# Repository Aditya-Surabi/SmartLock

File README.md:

# SmartLock

Smartphone controlled door locking system.

Hardware List
- Arduino Nano
- ESP8266
- Servo
- LM317 LDO 3.3V Voltage Regulator
- Deadbolt
- Battery (Capacity TBD)

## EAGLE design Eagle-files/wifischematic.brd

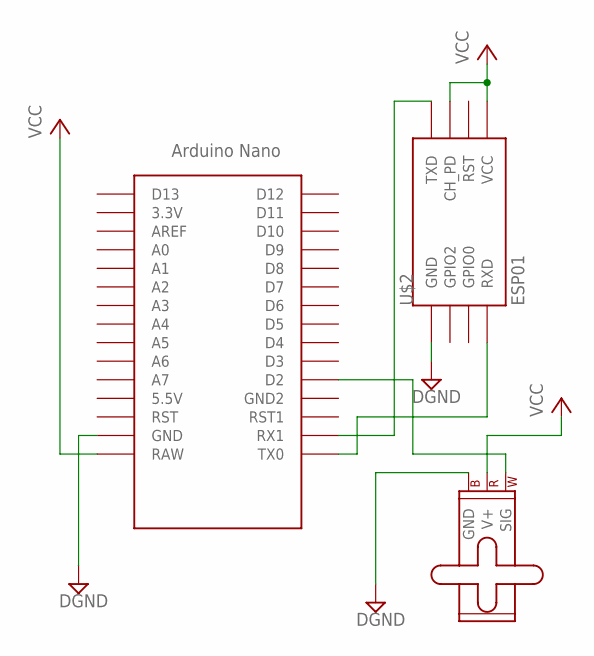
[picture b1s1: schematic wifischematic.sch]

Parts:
M1: SMALL_SERVO; 1X03
U$1: NANO
U$2: ESP01

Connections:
DGND: M1.3 (GND), U$1.GND, U$2.GND
unnamed: U$1.TX0, U$2.RX (RXD)
unnamed: U$1.RX1, U$2.TX (TXD)
unnamed: M1.1 (SIG), U$1.D2
VCC: M1.2 (V+), U$1.RAW, U$2.CH_PD, U$2.VCC

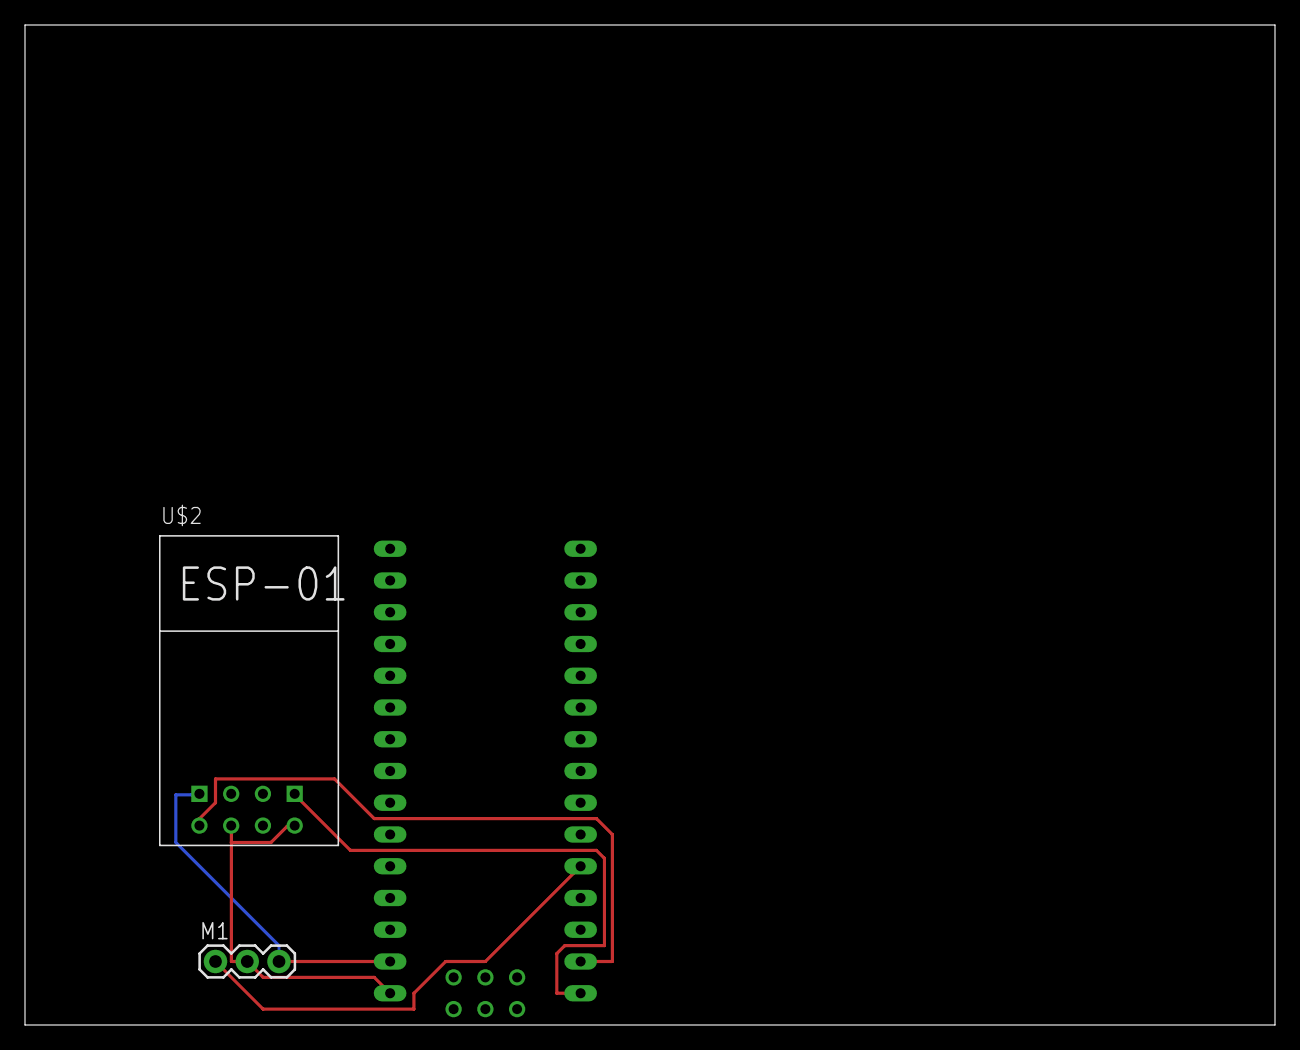
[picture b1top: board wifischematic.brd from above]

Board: 2 copper layers, 100.0 x 80.0 mm, 3 parts (0 on the bottom side), 5 nets.

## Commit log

2016-09-08 Added eagle files
2016-09-08 Added node files
2016-09-08 Added gitignore file
2016-09-08 updated nodelock

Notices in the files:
parts and their libraries:
SparkFun-Electromechanical: Licensing: Creative Commons ShareAlike 4.0 International - https://creativecommons.org/licenses/by-sa/4.0
